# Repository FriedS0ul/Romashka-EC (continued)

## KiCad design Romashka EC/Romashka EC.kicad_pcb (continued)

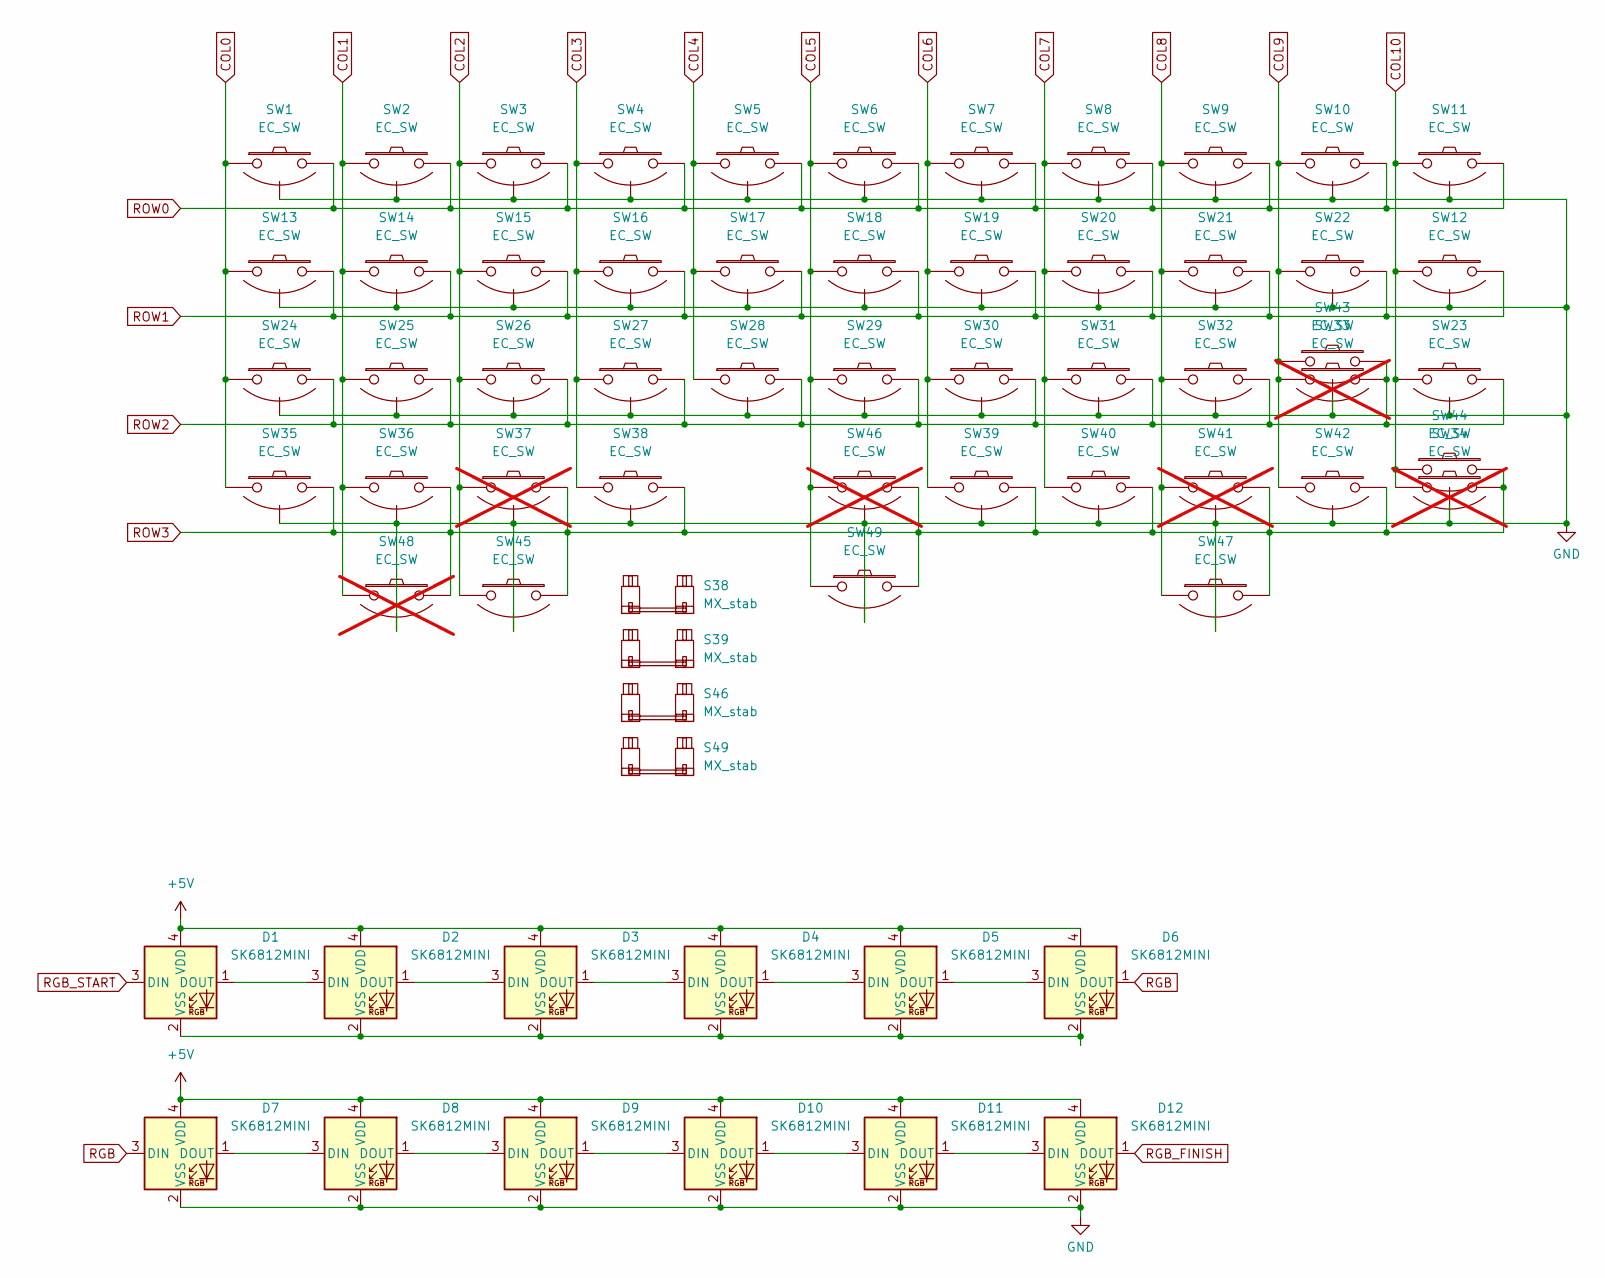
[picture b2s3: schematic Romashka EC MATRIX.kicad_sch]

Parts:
D1, D2, D3, D4, D5, D6, D7, D8, D9, D10, D11, D12: SK6812MINI; LED_SK6812MINI_PLCC4_3.5x3.5mm_P1.75mm
S38: MX_stab; STAB_MX_2.25u
S39: MX_stab; STAB_MX_2.75u
S46: MX_stab; STAB_MX_6.25u
S49: MX_stab; STAB_MX_7u
SW1, SW2, SW3, SW4, SW5, SW8, SW9, SW10, SW13, SW14, SW15, SW16, SW17, SW18, SW19, SW20, SW21, SW22, SW23, SW24, SW25, SW26, SW27, SW28, SW29, SW30, SW31, SW32, SW42: EC_SW; ecs_pad_1U_hybrid_hotswap_V3
SW6, SW7, SW11, SW12, SW35, SW38, SW39, SW40: EC_SW; ecs_pad_1U_hybrid_hotswap_V3_switched_sides
SW33, SW34, SW37, SW41, SW48: EC_SW; ecs_pad_1U_hybrid_hotswap_V2; not fitted
SW36, SW43, SW44, SW45, SW47: EC_SW; ecs_pad_hybrid_hotswap_2.381_V3
SW46: EC_SW; ecs_pad_1U_hybrid_hotswap_V2_switched_sides; not fitted
SW49: EC_SW; ecs_pad_hybrid_hotswap_7.144_V3

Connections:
+5V: D1.4 (VDD), D2.4 (VDD), D3.4 (VDD), D4.4 (VDD), D5.4 (VDD), D6.4 (VDD), D7.4 (VDD), D8.4 (VDD), D9.4 (VDD), D10.4 (VDD), D11.4 (VDD), D12.4 (VDD); also elsewhere on the board
COL0: SW1.1, SW13.1, SW24.1, SW35.1; also elsewhere on the board
COL1: SW2.1, SW14.1, SW25.1, SW36.1, SW48.1; also elsewhere on the board
COL2: SW3.1, SW15.1, SW26.1, SW37.1, SW45.1; also elsewhere on the board
COL3: SW4.1, SW16.1, SW27.1, SW38.1; also elsewhere on the board
COL4: SW5.1, SW17.1, SW28.1; also elsewhere on the board
COL5: SW6.1, SW18.1, SW29.1, SW46.1, SW49.1; also elsewhere on the board
COL6: SW7.1, SW19.1, SW30.1, SW39.1; also elsewhere on the board
COL7: SW8.1, SW20.1, SW31.1, SW40.1; also elsewhere on the board
COL8: SW9.1, SW21.1, SW32.1, SW41.1, SW47.1; also elsewhere on the board
COL9: SW10.1, SW22.1, SW33.1, SW42.1, SW43.1; also elsewhere on the board
COL10: SW11.1, SW12.1, SW23.1, SW34.1, SW44.1; also elsewhere on the board
GND: D7.2 (VSS), D8.2 (VSS), D9.2 (VSS), D10.2 (VSS), D11.2 (VSS), D12.2 (VSS), SW1.3 (SG), SW2.3 (SG), SW3.3 (SG), SW4.3 (SG), SW5.3 (SG), SW6.3 (SG), SW7.3 (SG), SW8.3 (SG), SW9.3 (SG), SW10.3 (SG), SW11.3 (SG), SW12.3 (SG), SW13.3 (SG), SW14.3 (SG), SW15.3 (SG), SW16.3 (SG), SW17.3 (SG), SW18.3 (SG), SW19.3 (SG), SW20.3 (SG), SW21.3 (SG), SW22.3 (SG), SW23.3 (SG), SW24.3 (SG), SW25.3 (SG), SW26.3 (SG), SW27.3 (SG), SW28.3 (SG), SW29.3 (SG), SW30.3 (SG), SW31.3 (SG), SW32.3 (SG), SW33.3 (SG), SW34.3 (SG), SW35.3 (SG), SW36.3 (SG), SW37.3 (SG), SW38.3 (SG), SW39.3 (SG), SW40.3 (SG), SW41.3 (SG), SW42.3 (SG), SW43.3 (SG), SW44.3 (SG), SW45.3 (SG), SW46.3 (SG), SW47.3 (SG), SW48.3 (SG), SW49.3 (SG); also elsewhere on the board
unnamed: D1.1 (DOUT), D2.3 (DIN)
unnamed: D1.2 (VSS), D2.2 (VSS), D3.2 (VSS), D4.2 (VSS), D5.2 (VSS), D6.2 (VSS)
unnamed: D2.1 (DOUT), D3.3 (DIN)
unnamed: D3.1 (DOUT), D4.3 (DIN)
unnamed: D4.1 (DOUT), D5.3 (DIN)
unnamed: D5.1 (DOUT), D6.3 (DIN)
unnamed: D7.1 (DOUT), D8.3 (DIN)
unnamed: D8.1 (DOUT), D9.3 (DIN)
unnamed: D9.1 (DOUT), D10.3 (DIN)
unnamed: D10.1 (DOUT), D11.3 (DIN)
unnamed: D11.1 (DOUT), D12.3 (DIN)
RGB: D6.1 (DOUT), D7.3 (DIN)
RGB_FINISH: D12.1 (DOUT)
RGB_START: D1.3 (DIN)
ROW0: SW1.2, SW2.2, SW3.2, SW4.2, SW5.2, SW6.2, SW7.2, SW8.2, SW9.2, SW10.2, SW11.2; also elsewhere on the board
ROW1: SW12.2, SW13.2, SW14.2, SW15.2, SW16.2, SW17.2, SW18.2, SW19.2, SW20.2, SW21.2, SW22.2; also elsewhere on the board
ROW2: SW23.2, SW24.2, SW25.2, SW26.2, SW27.2, SW28.2, SW29.2, SW30.2, SW31.2, SW32.2, SW33.2, SW43.2; also elsewhere on the board
ROW3: SW34.2, SW35.2, SW36.2, SW37.2, SW38.2, SW39.2, SW40.2, SW41.2, SW42.2, SW44.2, SW45.2, SW46.2, SW47.2, SW48.2, SW49.2; also elsewhere on the board

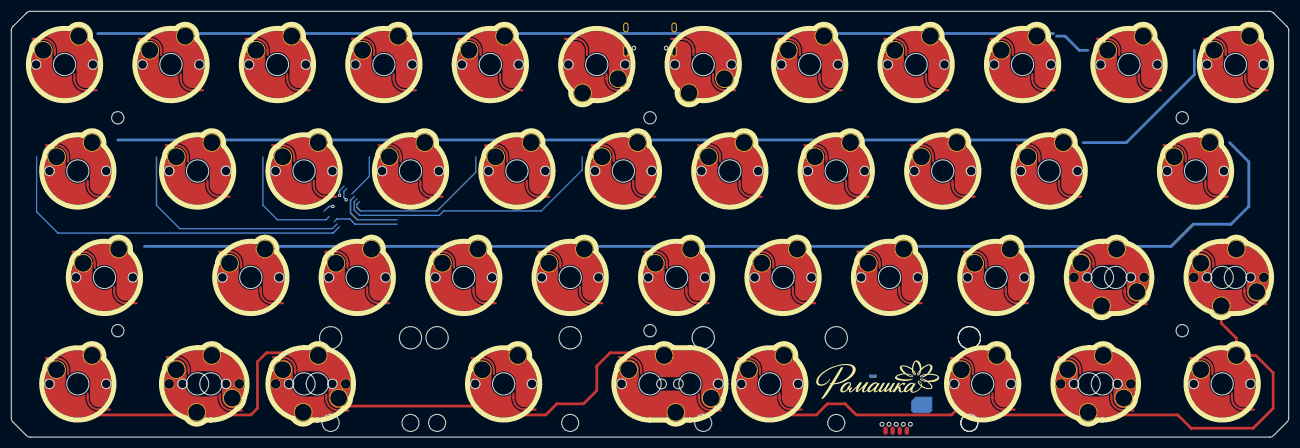
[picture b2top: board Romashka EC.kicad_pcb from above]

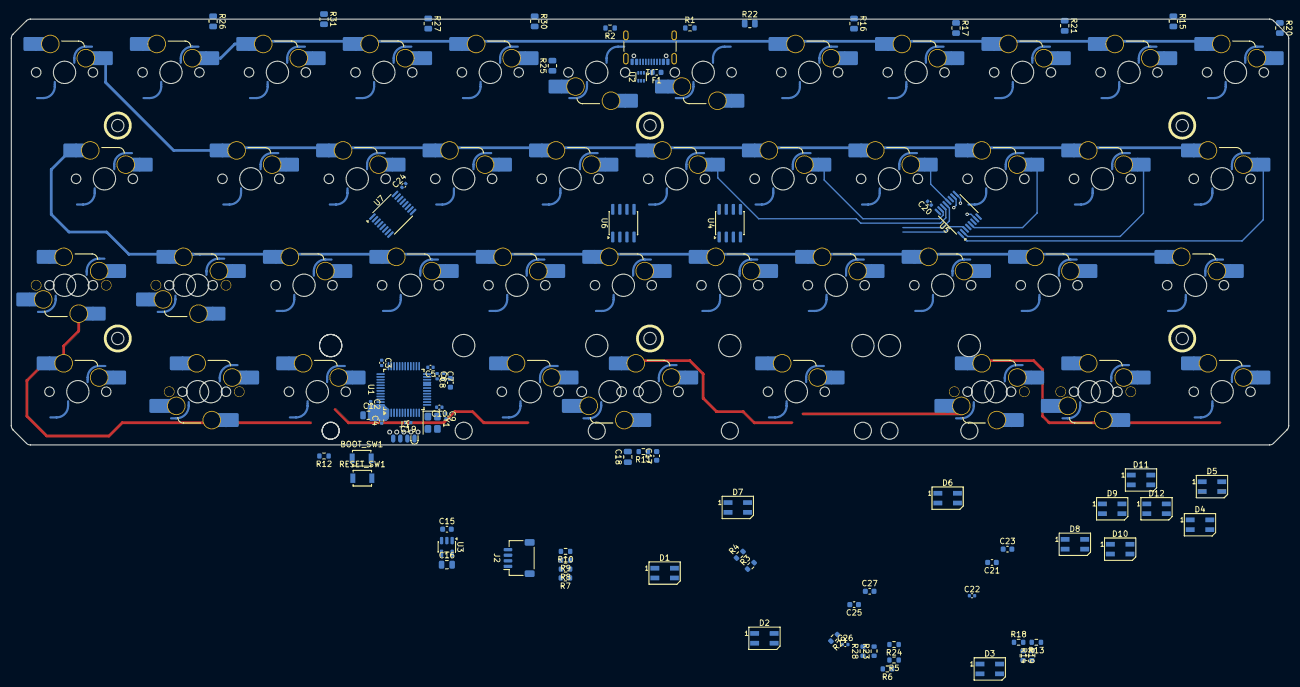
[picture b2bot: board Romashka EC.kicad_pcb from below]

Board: 2 copper layers, 228.6 x 76.2 mm, 127 parts (80 on the bottom side), 69 nets.

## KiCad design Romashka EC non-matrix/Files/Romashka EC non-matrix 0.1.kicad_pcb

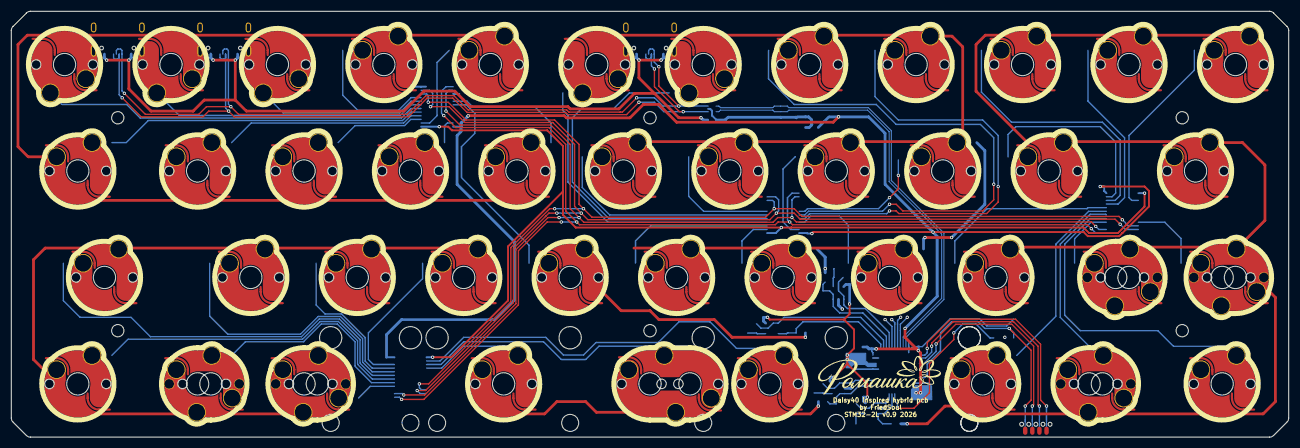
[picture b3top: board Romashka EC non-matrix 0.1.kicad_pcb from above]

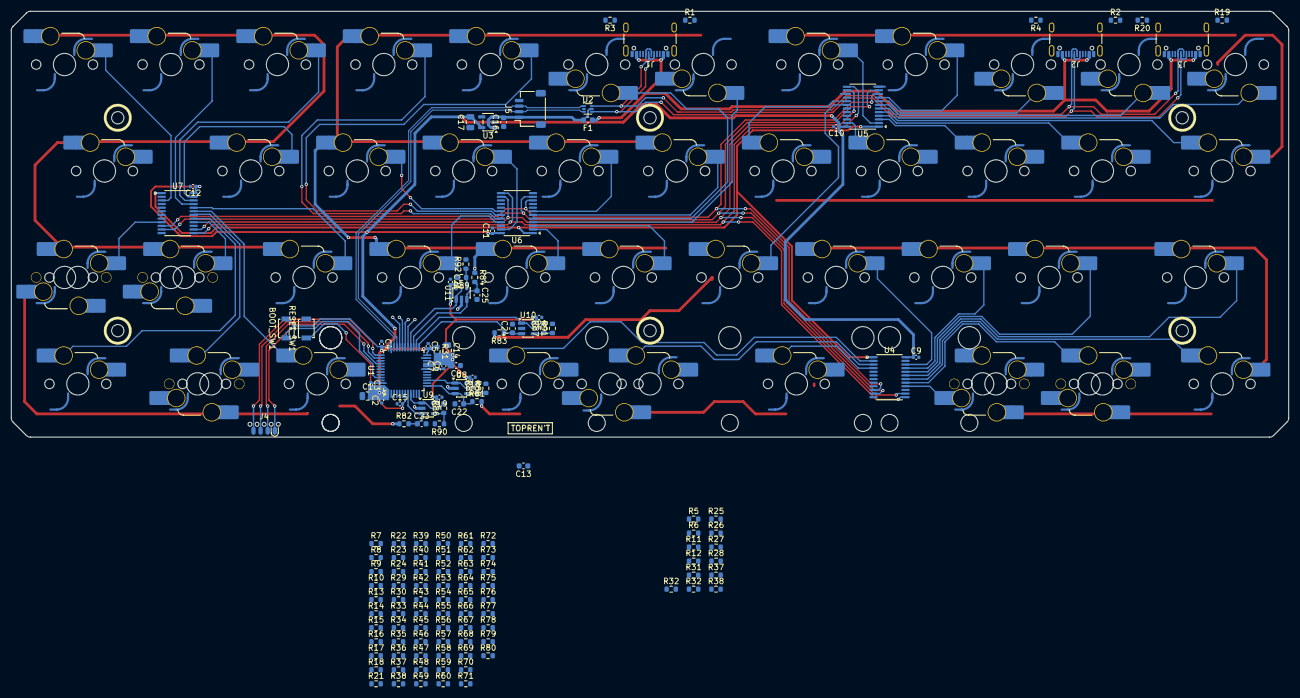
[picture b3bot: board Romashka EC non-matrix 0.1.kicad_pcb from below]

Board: 2 copper layers, 228.6 x 76.2 mm, 187 parts (140 on the bottom side), 105 nets.

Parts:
BOOT_SW1: Omron b3u; SW_SPST_B3U-1000P
C1, C14, C17: 10uF; C_0805_2012Metric
C2, C3, C4, C5, C6, C7, C9, C10, C11, C12, C15, C18, C19, C20, C21: 100nF; C_0402_1005Metric
C8, C13, C16: 1uF; C_0603_1608Metric
C22, C23, C24, C25: 470pF; C_0603_1608Metric
F1: 500mA; Fuse_0603_1608Metric
J1: Daisy40; USB_C_Receptacle_GCT_USB4105-xx-A_16P_TopMnt_Horizontal
J2: RS40; USB_C_Receptacle_GCT_USB4105-xx-A_16P_TopMnt_Horizontal
J3: JJ40; USB_C_Receptacle_GCT_USB4105-xx-A_16P_TopMnt_Horizontal
J4: SOICbite; SOICbite_footprint
J5: JSB USB; JST_SH_SM04B-SRSS-TB_1x04-1MP_P1.00mm_Horizontal
R1, R2, R3, R4, R19, R20: 5.1k; R_0603_1608Metric
R5, R6, R11, R12, R25, R26, R27, R28, R31, R32, R37#2, R38#2, R81, R82, R83, R84, R88, R90, R91, R92: 330; R_0603_1608Metric
R7, R8, R9, R10, R13, R14, R15, R16, R17, R18, R21, R22, R23, R24, R29, R30, R33, R34, R35, R36, R37, R38, R39, R40, R41, R42, R43, R44, R45, R46, R47, R48, R49, R50, R51, R52, R53, R54, R55, R56, R57, R58, R59, R60, R61, R62, R63, R64, R65, R66, R67, R68, R69, R70, R71, R72, R73, R74, R75, R76, R77, R78, R79, R80: 100K; R_0603_1608Metric
R31#2: 10R; R_0603_1608Metric
R32#2: 33k; R_0603_1608Metric
R85, R86, R87, R89: 33K; R_0603_1608Metric
RESET_SW1: Omron b3u; SW_SPST_B3U-1000P
S38: MX_stab; STAB_MX_2.25u
S39: MX_stab; STAB_MX_2.75u
S46: MX_stab; STAB_MX_6.25u
S49: MX_stab; STAB_MX_7u
SW1, SW2, SW3, SW6, SW7, SW13, SW14, SW15, SW16, SW17, SW35, SW38, SW39, SW40, SW42: EC_SW; ecs_pad_1U_hybrid_hotswap_V3
SW4, SW5, SW8, SW9, SW10, SW11, SW12, SW18, SW19, SW20, SW21, SW22, SW23, SW24, SW25, SW26, SW27, SW28, SW29, SW30, SW31, SW32: EC_SW; ecs_pad_1U_hybrid_hotswap_V3_switched_sides
SW36, SW43, SW44, SW45, SW47: EC_SW; ecs_pad_hybrid_hotswap_2.381_V3
SW49: EC_SW; ecs_pad_hybrid_hotswap_7.144_V3
U1: STM32G474CBTx; LQFP-48_7x7mm_P0.5mm
U2: USBLC6-2P6; SOT-563
U3: TPS7A2033; SOT-23-5
U4, U5, U6, U7: HEF4067BTT; TSSOP-24_4.4x7.8mm_P0.65mm
U8, U9, U10, U11: TLV9061xDBV; SOT-23-5

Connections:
+3.3V: BOOT_SW1.2 (B), C1.2, C2.2, C3.2, C4.2, C5.2, C9.1, C10.1, C11.1, C12.1, C13.2, C17.2, J4.8, R31#2.1, U1.1 (VBAT), U1.24 (VDD), U1.36 (VDD), U1.48 (VDD), U3.5 (OUT), U4.24 (VDD), U5.24 (VDD), U6.24 (VDD), U7.24 (VDD)
+3.3VA: C6.2, C7.2, C8.2, C14.2, C18.2, C19.2, C20.2, C21.2, R31#2.2, U1.20 (VREF+), U1.21 (VDDA), U8.5 (V+), U9.5 (V+), U10.5 (V+), U11.5 (V+)
+5V: C16.2, F1.2, J5.1, U2.5 (VBUS), U3.1 (IN), U3.3 (EN)
+5V_USB: F1.1, J1.A4 (VBUS), J1.A9 (VBUS), J1.B4 (VBUS), J1.B9 (VBUS), J2.A4 (VBUS), J2.A9 (VBUS), J2.B4 (VBUS), J2.B9 (VBUS), J3.A4 (VBUS), J3.A9 (VBUS), J3.B4 (VBUS), J3.B9 (VBUS)
ADC0: R5.2, R85.2, U1.15 (PA7), U8.1
ADC1: R6.2, R87.2, U1.26 (PB12), U10.1
ADC2: R11.2, R89.2, U1.28 (PB14), U11.1
ADC3: R12.2, R86.2, U1.9 (PA1), U9.1
BOOT0: BOOT_SW1.1 (A), J4.1, R32#2.1, U1.45 (PB8)
D+: J5.3, U1.34 (PA12), U2.1 (I/O1)
D-: J5.2, U1.33 (PA11), U2.3 (I/O2)
DISCHARGE0: C22.1, R81.1, U1.13 (PA5), U8.3 (+)
DISCHARGE1: C24.1, R83.1, U1.25 (PB11), U10.3 (+)
DISCHARGE2: C25.1, R84.2, U1.27 (PB13), U11.3 (+)
DISCHARGE3: C23.1, R82.2, U1.8 (PA0), U9.3 (+)
DM_USB: J1.A7 (D-), J1.B7 (D-), J2.A7 (D-), J2.B7 (D-), J3.A7 (D-), J3.B7 (D-), U2.4 (I/O2)
DP_USB: J1.A6 (D+), J1.B6 (D+), J2.A6 (D+), J2.B6 (D+), J3.A6 (D+), J3.B6 (D+), U2.6 (I/O1)
GND: C1.1, C2.1, C3.1, C4.1, C5.1, C6.1, C7.1, C8.1, C9.2, C10.2, C11.2, C12.2, C13.1, C14.1, C15.1, C16.1, C17.1, C18.1, C19.1, C20.1, C21.1, C22.2, C23.2, C24.2, C25.2, J1.A1 (GND), J1.A12 (GND), J1.B1 (GND), J1.B12 (GND), J1.S1 (SHIELD), J2.A1 (GND), J2.A12 (GND), J2.B1 (GND), J2.B12 (GND), J2.S1 (SHIELD), J3.A1 (GND), J3.A12 (GND), J3.B1 (GND), J3.B12 (GND), J3.S1 (SHIELD), J4.5, J5.4, R1.2, R2.2, R3.2, R4.2, R7.1, R8.1, R9.1, R10.1, R13.1, R14.1, R15.1, R16.1, R17.1, R18.1, R19.2, R20.2, R21.1, R22.1, R23.1, R24.1, R29.1, R30.1, R32#2.2, R33.1, R34.1, R35.1, R36.1, R37.1, R38.1, R39.1, R40.1, R41.2, R42.2, R43.2, R44.2, R45.2, R46.2, R47.2, R48.2, R49.2, R50.2, R51.2, R52.2, R53.2, R54.2, R55.2, R56.2, R57.2, R58.2, R59.2, R60.2, R61.2, R62.2, R63.2, R64.2, R65.2, R66.2, R67.2, R68.2, R69.2, R70.2, R71.2, R72.2, R73.2, R74.2, R75.2, R76.2, R77.2, R78.2, R79.2, R80.2, R88.2, R90.2, R91.2, R92.2, RESET_SW1.2 (B), SW1.3 (SG), SW2.3 (SG), SW3.3 (SG), SW4.3 (SG), SW5.3 (SG), SW6.3 (SG), SW7.3 (SG), SW8.3 (SG), SW9.3 (SG), SW10.3 (SG), SW11.3 (SG), SW12.3 (SG), SW13.3 (SG), SW14.3 (SG), SW15.3 (SG), SW16.3 (SG), SW17.3 (SG), SW18.3 (SG), SW19.3 (SG), SW20.3 (SG), SW21.3 (SG), SW22.3 (SG), SW23.3 (SG), SW24.3 (SG), SW25.3 (SG), SW26.3 (SG), SW27.3 (SG), SW28.3 (SG), SW29.3 (SG), SW30.3 (SG), SW31.3 (SG), SW32.3 (SG), SW35.3 (SG), SW36.3 (SG), SW38.3 (SG), SW39.3 (SG), SW40.3 (SG), SW42.3 (SG), SW43.3 (SG), SW44.3 (SG), SW45.3 (SG), SW47.3 (SG), SW49.3 (SG), U1.19 (VSSA), U1.23 (VSS), U1.35 (VSS), U1.47 (VSS), U2.2 (GND), U3.2 (GND), U4.12 (VSS), U4.15 (~E), U5.12 (VSS), U5.15 (~E), U6.12 (VSS), U6.15 (~E), U7.12 (VSS), U7.15 (~E), U8.2 (V-), U9.2 (V-), U10.2 (V-), U11.2 (V-)
MUX0_D0: R15.2, U4.9 (Y0)
MUX0_D1: R7.2, U4.8 (Y1)
MUX0_D2: R16.2, U4.7 (Y2)
MUX0_D3: R8.2, U4.6 (Y3)
MUX0_D4: R17.2, U4.5 (Y4)
MUX0_D5: R9.2, SW38.2, U4.4 (Y5)
MUX0_D6: R55.1, SW49.2, U4.3 (Y6)
MUX0_D7: R45.1, SW39.2, U4.2 (Y7)
MUX0_D8: R54.1, U4.23 (Y8)
MUX0_D9: R44.1, SW27.2, U4.22 (Y9)
MUX0_D10: R53.1, SW26.2, U4.21 (Y10)
MUX0_D11: R43.1, SW25.2, U4.20 (Y11)
MUX0_D12: R52.1, SW24.2, U4.19 (Y12)
MUX0_D13: R42.1, SW35.2, U4.18 (Y13)
MUX0_D14: R51.1, SW36.2, U4.17 (Y14)
MUX0_D15: R41.1, SW45.2, U4.16 (Y15)
MUX0_IN: R25.1, U4.1 (Z), U5.1 (Z), U6.1 (Z), U7.1 (Z)
MUX1_D0: R23.2, SW4.2, U5.9 (Y0)
MUX1_D1: R10.2, SW3.2, U5.8 (Y1)
MUX1_D2: R24.2, SW2.2, U5.7 (Y2)
MUX1_D3: R13.2, SW1.2, U5.6 (Y3)
MUX1_D4: R29.2, SW13.2, U5.5 (Y4)
MUX1_D5: R14.2, SW14.2, U5.4 (Y5)
MUX1_D6: R65.1, SW15.2, U5.3 (Y6)
MUX1_D7: R50.1, SW5.2, U5.2 (Y7)
MUX1_D8: R64.1, SW16.2, U5.23 (Y8)
MUX1_D9: R49.1, U5.22 (Y9)
MUX1_D10: R63.1, U5.21 (Y10)
MUX1_D11: R48.1, U5.20 (Y11)
MUX1_D12: R62.1, U5.19 (Y12)
MUX1_D13: R47.1, SW28.2, U5.18 (Y13)
MUX1_D14: R61.1, SW17.2, U5.17 (Y14)
MUX1_D15: R46.1, U5.16 (Y15)
MUX2_D0: R35.2, U6.9 (Y0)
MUX2_D1: R18.2, U6.8 (Y1)
MUX2_D2: R36.2, SW19.2, U6.7 (Y2)
MUX2_D3: R21.2, SW18.2, U6.6 (Y3)
MUX2_D4: R37.2, SW7.2, U6.5 (Y4)
MUX2_D5: R22.2, SW6.2, U6.4 (Y5)
MUX2_D6: R75.1, SW29.2, U6.3 (Y6)
MUX2_D7: R60.1, SW30.2, U6.2 (Y7)
MUX2_D8: R74.1, SW20.2, U6.23 (Y8)
MUX2_D9: R59.1, U6.22 (Y9)
MUX2_D10: R73.1, SW31.2, U6.21 (Y10)
MUX2_D11: R58.1, SW9.2, U6.20 (Y11)
MUX2_D12: R72.1, SW8.2, U6.19 (Y12)
MUX2_D13: R57.1, SW21.2, U6.18 (Y13)
MUX2_D14: R71.1, U6.17 (Y14)
MUX2_D15: R56.1, U6.16 (Y15)
MUX3_D0: R38.2, SW44.2, U7.9 (Y0)
MUX3_D1: R30.2, U7.8 (Y1)
MUX3_D2: R39.2, U7.7 (Y2)
MUX3_D3: R33.2, U7.6 (Y3)
MUX3_D4: R40.2, U7.5 (Y4)
MUX3_D5: R34.2, U7.4 (Y5)
MUX3_D6: R80.1, SW12.2, U7.3 (Y6)
MUX3_D7: R70.1, SW23.2, U7.2 (Y7)
MUX3_D8: R79.1, SW22.2, U7.23 (Y8)
MUX3_D9: R69.1, SW10.2, U7.22 (Y9)
MUX3_D10: R78.1, SW11.2, U7.21 (Y10)
MUX3_D11: R68.1, SW32.2, U7.20 (Y11)
MUX3_D12: R77.1, SW40.2, U7.19 (Y12)
MUX3_D13: R67.1, SW47.2, U7.18 (Y13)
MUX3_D14: R76.1, SW42.2, U7.17 (Y14)
MUX3_D15: R66.1, SW43.2, U7.16 (Y15)
MUX_S0: U1.44 (PB7), U4.10 (A0), U5.10 (A0), U6.10 (A0), U7.10 (A0)
MUX_S1: U1.43 (PB6), U4.11 (A1), U5.11 (A1), U6.11 (A1), U7.11 (A1)
MUX_S2: U1.42 (PB5), U4.14 (A2), U5.14 (A2), U6.14 (A2), U7.14 (A2)
MUX_S3: U1.41 (PB4), U4.13 (A3), U5.13 (A3), U6.13 (A3), U7.13 (A3)
unnamed: J1.A5 (CC1), R1.1
unnamed: J1.B5 (CC2), R3.1
unnamed: J2.A5 (CC1), R2.1
unnamed: J2.B5 (CC2), R4.1
unnamed: J3.A5 (CC1), R19.1
unnamed: J3.B5 (CC2), R20.1
unnamed: R85.1, R88.1, U8.4 (-)
unnamed: R86.1, R90.1, U9.4 (-)
unnamed: R87.1, R91.1, U10.4 (-)
unnamed: R89.1, R92.1, U11.4 (-)
RESET: C15.2, J4.6, RESET_SW1.1 (A), U1.7 (PG10)
SENSE0: R81.2, SW24.1, SW25.1, SW26.1, SW27.1, SW35.1, SW36.1, SW38.1, SW39.1, SW45.1, SW49.1
SENSE1: R83.2, SW1.1, SW2.1, SW3.1, SW4.1, SW5.1, SW13.1, SW14.1, SW15.1, SW16.1, SW17.1, SW28.1
SENSE2: R84.1, SW6.1, SW7.1, SW8.1, SW9.1, SW18.1, SW19.1, SW20.1, SW21.1, SW29.1, SW30.1, SW31.1
SENSE3: R82.1, SW10.1, SW11.1, SW12.1, SW22.1, SW23.1, SW32.1, SW40.1, SW42.1, SW43.1, SW44.1, SW47.1
SWCLK: J4.3, U1.38 (PA14)
SWDIO: J4.4, U1.37 (PA13)
SWO: J4.2, U1.40 (PB3)

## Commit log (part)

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2026-04-17 17.04.2026: setup
2026-04-19 19.04.2026: setup
2026-04-20 20.04.2026: setup
2026-04-20 21.04.2026: footprints
2026-04-21 21.04.2026: non-matrix variant
2026-04-21 21.04.2026 09:06
2026-04-21 21.04.2026 something something
2026-04-21 22.04.2026
2026-04-22 22.04.2026 something something
2026-04-23 23.04.2026
2026-04-24 24.04.2026
2026-04-27 27.04.2026
2026-04-28 28.04.2026
2026-04-29 29.04.2026
2026-04-30 30.04.2026
2026-05-05 05.05.2026
2026-05-14 14.05.2026
2026-05-15 15.05.2026
2026-05-17 17.05.2026
2026-05-18 18.05.2026
2026-05-18 19.05.2026
2026-05-20 20.05.2026
2026-05-22 22.05.2026
2026-05-24 25.05.2026
2026-05-26 26.05.2026
2026-06-22 22.06.2026
